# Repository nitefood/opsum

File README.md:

# OPSUM - The Open PSU Meter project

OPSUM is a **DC voltmeter and ammeter board** with 4mm banana socket inputs, that enables measuring and logging **voltage, current and power**, even when using a bench PSU that has no builtin telemetry feature. Communication between the board and the host happens via **UART protocol** over a dedicated USB port that is **galvanically isolated** from the PSU/DUT (*power supply unit and device under test*) side of the PCB, in order to protect the host-side (PC) from potentially destructive shorts or spikes happening on the DUT side.

This repository is structured as a **monorepo**: hardware design files, enclosure CAD files, firmware, host-side GUI tools, release binaries, communication protocol documentation, and third-party GUIs are kept together so you can build, flash, and evolve the project starting from a single source of truth.

## Features

#### Current

- **Real-time voltage, current, and power monitoring** based on the [INA226](https://www.ti.com/product/INA226) monitor IC and the [ESP32-S3](https://www.espressif.com/en/products/socs/esp32-s3) SoC.
- [Kelvin-sensed](https://en.wikipedia.org/wiki/Four-terminal_sensing) shunt layout and full noise filtering (as per TI's [datasheet](https://www.ti.com/lit/ds/symlink/ina226.pdf), chapter *6.4.2 "Filtering and Input Considerations"*) for improved measurement accuracy.
- **Reverse-polarity**, **overvoltage**, and **negative-voltage** protection circuitry.
- PMOS input protection stage with zener-clamped gate drive.
- TVS + Schottky protected INA VBUS input.
- **Galvanic isolation** protecting the host-side USB port from the PSU/DUT side.
- Handles up to **36 V** bus voltage and **20 A** current.
- Compact, low-cost, fully **open source hardware, firmware and software** project.

#### Planned

- I<sup>2</sup>C display showing real time telemetry from the board *(I<sup>2</sup>C pin header for the display is already present on the PCB, only needs designing the enclosure lid opening and in-firmware support)*

## Images
Enclosure render (outside) | Enclosure render (inside)
| - | - |
|  |  |

PCB Layout | PCB 3D View
| - | - |
 |  |

3D printed enclosure (top view) | 3D printed enclosure (sockets visible)
| - | - |
|  |  |

#### 3D printed enclosure (internal 12AWG wiring)

#### [Farmtech's PSU monitor](/third_party_tools/farmtech/) displaying telemetry coming from a live OPSUM board

---

## Quick Start

If you want to build the project yourself, the step-by-step approach is:

1. **Manufacture the board** using a third party PCB fab house (I've used [JLCPCB](https://jlcpcb.com/?from=DUYEWB) with great results, so tolerances and specs are guaranteed to comply with their capabilities, but any fab house should be easily capable to manufacture this board). **Gerbers, BOM and CPL** files alongside required production settings and instructions for PCB manufacturing and assembly are all in the [hardware](/hardware/) section.
	> Disclaimer: the JLCPCB link above is a referral URL, I get a little kickback if you use it to subscribe or buy from them. Thanks for your support!
2. **Solder the remaining through-hole components on the PCB** using the instruction under [howto-build](/howto-build/). I've included a bill of material for THT and hand-assembly components required to complete the project, complete with links to AliExpress to source them.
3. **First-flash the new ESP32-S3 board** with the `-FULL` image (using `esptool`). Prebuilt binaries and usage instructions for `esptool` are in the [dist](dist/) section.
4. **3D print the enclosure and assemble the finished product**. Instructions are under [enclosure](/enclosure/).
5. **Connect the USB port to your PC and use a client-side program** to interface with the OPSUM board and receve its readings. I've included a [minimal GUI](dist/opsum_gui.exe), alongside with fully featured [third party tools](third_party_tools/) compatibile with OPSUM's core firmware [protocol](./protocol-specs/core-uart.md).

If you want to flash a different firmware, or update/reflash the core firmware in the future, there is **no need to disassemble the board** to access the native MCU USB port. Just use the **isolated USB port** with the included [flash tool](dist/flashtool.exe), and reflash the board using a `-OTA` image. OPSUM's main firmware OTA image is packaged under [dist](dist/) as well.

## Open Tooling Approach

This repository includes everything, ranging from the basic OPSUM GUI plus third-party client-side tools that support the Core firmware communication protocol, to enclosure CAD models, PCB layout design files, assembly guides and protocol specification documentation.

You are free to use whichever compatible client (or firmware) matches your needs.

## Repository Layout

| Folder | Contents |
| - | - |
| [dist/](dist/) | release binaries + compilation and flash instructions |
| [protocol-specs/](protocol-specs/) | **DFU** (flashing) and **UART** (runtime communication with the host) protocol specs |
| [src/Firmware/](src/Firmware/) | **Core** (main) and **DFU** (flash update mode) firmware source code |
| [src/GUI/](src/GUI/) | host-side GUI tools source code root folder |
| [src/GUI/flash-tool/](src/GUI/flash-tool/) | desktop DFU flashing GUI source code |
| [src/GUI/opsum-gui/](src/GUI/opsum-gui/) | minimal OPSUM runtime GUI frontend source code |
| [third_party_tools/](third_party_tools/) | bundled alternative host-side tools and board-side firmware binaries |
| [hardware/](hardware/) | schematic, PCB layout, BOM, CPL, Gerbers and manufacturing guide |
| [enclosure/](enclosure/) | CAD files for the OPSUM case |
| [howto-build/](howto-build/) | Manual assembly and soldering step-by-step instructions for the OPSUM board project |

## Contributing

**OPSUM is inteded as an open, community driven project**. Anyone is welcome to contribute to it by creating or improving client-side tools, firmware, enclosure, PCB design, protocol specs or documentation!

## Acknowledgements

This project was born out of the desire to improve my PCB design skills, and to document a complete DIY approach to getting a full featured ammeter from scratch, instead of buying one.

In this endeavor, I've received a lot of precious support and ideas from the [JFIXX](https://www.youtube.com/@JFIXX1) community. If you want to join us to say hello, his [discord](https://discord.gg/TcsUshz67p) server is a welcoming and friendly place, full of very skilled and amazing techs!

## Supporting the project

If you like this project and want to support it, you can do so by clicking the button below. Thank you! <3

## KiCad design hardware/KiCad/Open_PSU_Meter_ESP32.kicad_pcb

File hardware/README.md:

# Hardware Design Files

---

---

## Folder contents

This folder hosts electrical and manufacturing design assets for the OPSUM PCB.

## CAD software used

- The OPSUM PCB was designed entirely using the [KiCad v10.0](https://www.kicad.org/) EDA software.

- PCBs were manufactured using [JLCPCB](https://jlcpcb.com/?from=DUYEWB).

	> Disclaimer: the JLCPCB link above is a referral URL, I get a little kickback if you use it to subscribe or buy from them. Thanks for your support!
- Production files were generated by using the excellent [kicad-jlcpb-tools](https://github.com/bouni/kicad-jlcpcb-tools) KiCad plugin.

## Folder structure

| Folder/File name | Content |
| - | - |
| [schematic/](./schematic/) | Full board schematic in .PDF format |
| [KiCad/](./KiCad/) | KiCad project files for schematic and PCB layout |
| [jlcpcb/](./jlcpcb/) | BOM (Bill of Materials), CPL (Component Placement List), Gerber manufacturing outputs |

## Step-by-step Manufacturing Guide (for JLCPCB)

1. Login to [JLCPCB](https://jlcpcb.com/?from=DUYEWB) and click the **Get Instant Quote** button
2. Click "Add gerber file" and upload the [Gerber .zip archive](./jlcpcb/production_files/GERBER-Open_PSU_Meter_ESP32.zip)
3. Layers count and PCB size will be both autodetected from the Gerber files. You can leave all settings as they are. Optionally, you may prefer setting `Surface Finish` to *LeadFree HASL*, but the default will do just fine
4. Scroll to the bottom of the page and enable the **PCB Assembly** toggle. Keep the default values there as well
5. Ensure you pick the desired **PCBA Qty** value: this will determine how many of the manufactured PCBs will also get their SMT components assembled
6. Click Next, then Next.
7. Add the [BOM](./jlcpcb/production_files/BOM-Open_PSU_Meter_ESP32.csv) and [CPL](./jlcpcb/production_files/CPL-Open_PSU_Meter_ESP32.csv) files, then click  **Process BOM & CPL**
8. Ignore the warning (*"The below parts won't be assembled due to data missing.
U3,PS1 designators don't exist in the BOM file."*). This is intentional, since those parts (ESP32-S3-Zero breakout board and isolated DC/DC converter) are to be sourced externally and hand soldered on the PCB. Refer to the [howto-build](../howto-build/) guide for details.
9. Review the matched parts and ensure all are in stock. Click Next.
10. **Carefully check part orientation on the board**. Sometimes their automated system fails to correctly orient the components on the pads. In my case, I had to re-orient **U1** and **Q1**. Just **click the component to select it**, and **press the space key** until they're in the correct orientation (the purple dot should align with the white silkscreen dot/arrow). They should look like this:

	| U1 | Q1 |
	| - | - |
	|  |  |
11. Click Next and pick "*Research/Education/DIY/Entertainment*" -> "*DIY Hobby Circuit Board - HS Code 902300*" from the product description dropdown, then click **Save to Cart**
12. Select the cart item (PCB Manufacture + PCBA) and proceed to Secure Checkout. You will be able to pick a shipping method, enter your shipping address, and complete the order.

## Hand Soldering Guide for through hole components

Once the board is manufactured and the enclosure is printed, refer to the [How To Build](../howto-build/) section to finish assembling the tool.

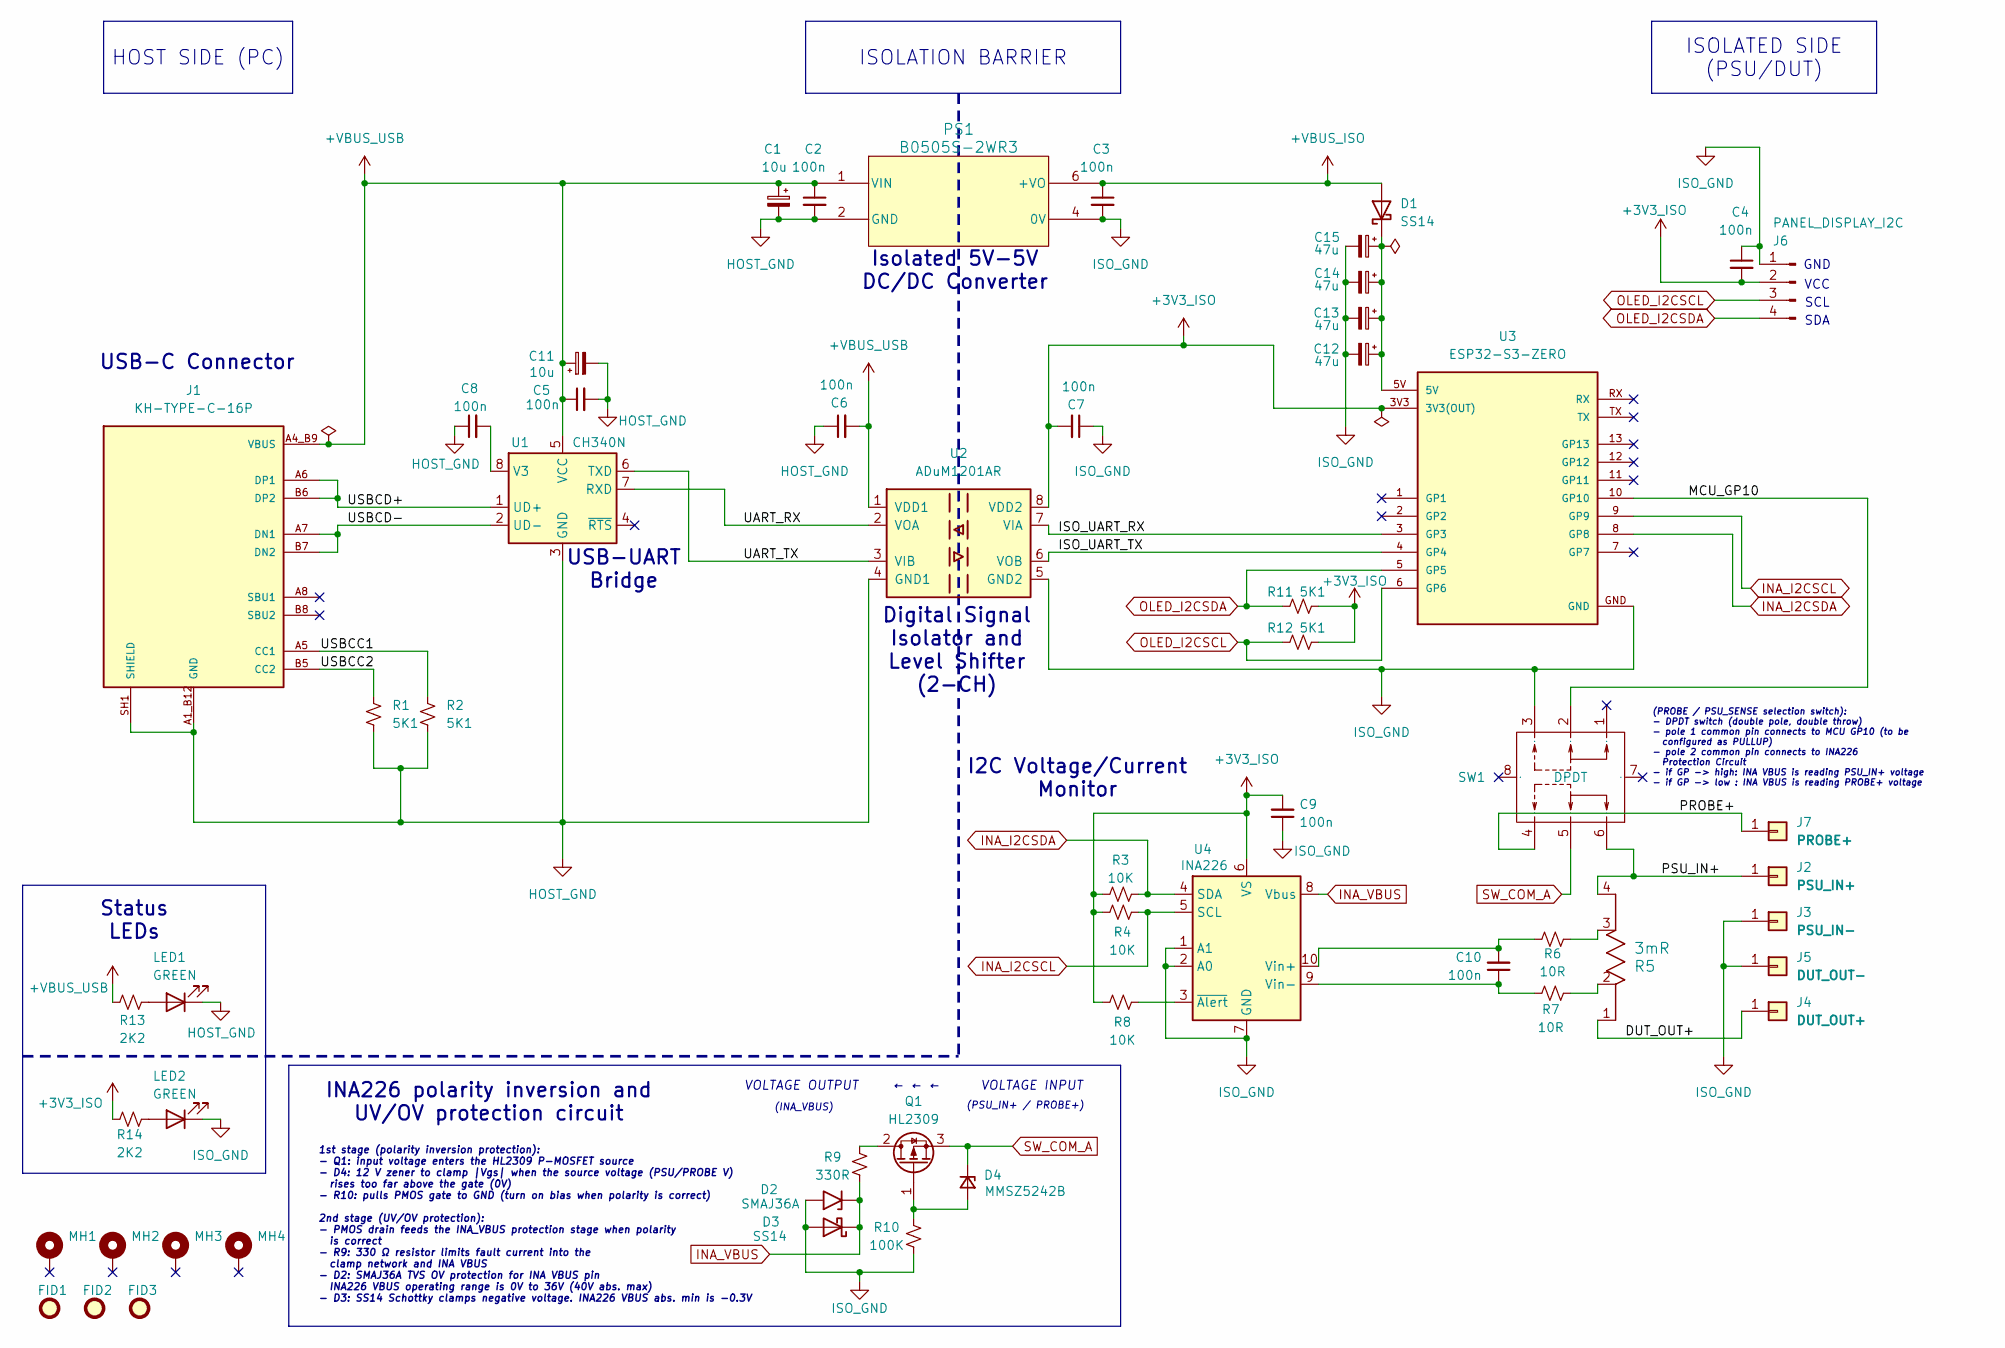
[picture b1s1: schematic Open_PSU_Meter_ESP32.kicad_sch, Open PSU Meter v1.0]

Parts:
C1, C11: 10u; C_1206_3216Metric; Manufacturer Part Number CL31A106KBHNNNE; LCSC C13585
C2, C3, C4, C5, C6, C7, C8, C9, C10: 100n; C_0603_1608Metric; Manufacturer Part Number CC0603KRX7R9BB104; LCSC C14663
C12, C13, C14, C15: 47u; C_1206_3216Metric; Manufacturer Part Number CL31A476MPHNNNE; LCSC C96123
D1, D3: SS14; D_SMA; Manufacturer Part Number SS14; LCSC C2480
D2: SMAJ36A; D_SMA; Manufacturer Part Number SMAJ36A; LCSC C19077550
D4: MMSZ5242B; D_SOD-123; Manufacturer Part Number MMSZ5242B; LCSC C19077426
FID1, FID2, FID3: Fiducial; Fiducial_1mm_Mask2mm
J1: KH-TYPE-C-16P; KINGHELM_KH-TYPE-C-16P; PARTREV A0; LCSC C709357
J2: PSU_IN+
J3: PSU_IN-
J4: DUT_OUT+
J5: DUT_OUT-
J6: PANEL_DISPLAY_I2C; PinHeader_1x04_P2.54mm_Vertical
J7: PROBE+
LED1, LED2: GREEN; LED_0805_2012Metric; Manufacturer Part Number KT-0805G; LCSC C2297
MH1, MH2, MH3, MH4: MountingHole_Pad; MountingHole_2.7mm_M2.5_Pad_Via
PS1: B0505S-2WR3; B_S-2WR2_MNS
Q1: HL2309; SOT-23-3; Manufacturer Part Number HL2309; LCSC C28646263
R1, R2, R11, R12: 5K1; R_0603_1608Metric; Manufacturer Part Number 0603WAF5101T5E; LCSC C23186
R3, R4, R8: 10K; R_0402_1005Metric; Manufacturer Part Number 0402WGF1002TCE; LCSC C25744
R5: 3mR; WSL3637_VIS; Manufacturer Part Number WSL36373L000FEA; LCSC C844085
R6, R7: 10R; R_0402_1005Metric; Manufacturer Part Number TC0225B100JTCC; LCSC C517445
R9: 330R; R_0402_1005Metric; Manufacturer Part Number 0402WGF3300TCE; LCSC C25104
R10: 100K; R_0402_1005Metric; Manufacturer Part Number 0402WGF1003TCE; LCSC C25741
R13, R14: 2K2; R_0603_1608Metric; Manufacturer Part Number 0603WAF2201T5E; LCSC C4190
SW1: DPDT; SW-TH_SK22D02G5; Manufacturer Part SK22D02G5; LCSC Part Name SK22D02G5
U1: CH340N; JEITA_SOIC-8_3.9x4.9mm_P1.27mm; Manufacturer Part Number CH340N; LCSC C2977777
U2: ADuM1201AR; SOIC-8_3.9x4.9mm_P1.27mm; Manufacturer Part Number ADUM1201ARZ-RL7; LCSC C9669
U3: ESP32-S3-ZERO; MODULE_ESP32-S3-ZERO; PARTREV NA
U4: INA226; TSSOP-10_3x3mm_P0.5mm; Manufacturer Part Number INA226AIDGSR; LCSC C49851

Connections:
+3V3_ISO: C4.2, C7.2, C9.2, J6.2, R3.1, R4.2, R8.2, R11.1, R12.1, R14.2, U2.8 (VDD2), U3.3V3 (3V3(OUT)), U4.6 (VS)
+VBUS_ISO: C3.1, D1.2 (A), PS1.6 (+VO)
+VBUS_USB: C1.1, C2.1, C5.1, C6.2, C11.1, J1.A4_B9 (VBUS), J1.A9_B4 (VBUS), PS1.1 (VIN), R13.1, U1.5 (VCC), U2.1 (VDD1)
/DUT_OUT+: J4.1, R5.1
/ISO_UART_RX: U2.7 (VIA), U3.3 (GP3)
/ISO_UART_TX: U2.6 (VOB), U3.4 (GP4)
/MCU_GP10: SW1.2, U3.10 (GP10)
/PROBE+: J7.1, SW1.4
/PSU_IN+: J2.1, R5.4, SW1.6
/UART_RX: U1.7 (RXD), U2.2 (VOA)
/UART_TX: U1.6 (TXD), U2.3 (VIB)
/USBCC1: J1.A5 (CC1), R2.1
/USBCC2: J1.B5 (CC2), R1.1
/USBCD+: J1.A6 (DP1), J1.B6 (DP2), U1.1 (UD+)
/USBCD-: J1.A7 (DN1), J1.B7 (DN2), U1.2 (UD-)
HOST_GND: C1.2, C2.2, C5.2, C6.1, C8.1, C11.2, J1.A1_B12 (GND), J1.A12_B1 (GND), J1.SH1 (SHIELD), J1.SH2 (SHIELD), J1.SH3 (SHIELD), J1.SH4 (SHIELD), LED1.1 (K), PS1.2 (GND), R1.2, R2.2, U1.3 (GND), U2.4 (GND1)
INA_I2CSCL: R4.1, U3.9 (GP9), U4.5 (SCL)
INA_I2CSDA: R3.2, U3.8 (GP8), U4.4 (SDA)
INA_VBUS: D2.1 (A1), D3.1 (K), R9.1, U4.8 (Vbus)
ISO_GND: C3.2, C4.1, C7.1, C9.1, C12.2, C13.2, C14.2, C15.2, D2.2 (A2), D3.2 (A), J3.1, J5.1, J6.1, LED2.1 (K), PS1.4 (0V), R10.2, SW1.3, U2.5 (GND2), U3.GND, U4.1 (A1), U4.2 (A0), U4.7 (GND)
unnamed: C12.1, C13.1, C14.1, C15.1, D1.1 (K), U3.5V
unnamed: D4.2 (A), Q1.1 (G), R10.1
unnamed: LED1.2 (A), R13.2
unnamed: LED2.2 (A), R14.1
unnamed: Q1.2 (D), R9.2
unnamed: R5.2, R7.2
unnamed: R5.3, R6.2
unnamed: C8.2, U1.8 (V3)
unnamed: C10.2, R6.1, U4.10 (Vin+)
unnamed: C10.1, R7.1, U4.9 (Vin-)
unnamed: R8.1, U4.3 (~Alert)
OLED_I2CSCL: J6.3, R12.2, U3.6 (GP6)
OLED_I2CSDA: J6.4, R11.2, U3.5 (GP5)
SW_COM_A: D4.1 (K), Q1.3 (S), SW1.5

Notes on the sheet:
SCL
(INA_VBUS)
(PSU_IN+ / PROBE+)
I2C Voltage/Current Monitor
Isolated 5V-5V DC/DC Converter
SDA
Status LEDs
Digital Signal Isolator and Level Shifter (2-CH)
VCC
VOLTAGE OUTPUT ← ← ← VOLTAGE INPUT
GND
INA226 polarity inversion and UV/OV protection circuit
1st stage (polarity inversion protection): - Q1: input voltage enters the HL2309 P-MOSFET source - D4: 12 V zener to clamp |Vgs| when the source voltage (PSU/PROBE V) rises too far above the gate (0V) - R10: pulls PMOS gate to GND (turn on bias when polarity is correct) 2nd stage (UV/OV protection)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
USB-UART Bridge
(PROBE / PSU_SENSE selection switch): - DPDT switch (double pole, double throw) - pole 1 common pin connects to MCU GP10 (to be configured as PULLUP) - pole 2 common pin connects to INA226 Protection Circuit - if GP -> high: INA VBUS is reading PSU_IN+ voltage - if GP -> low : INA VBUS is reading P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
USB-C Connector
ISOLATED SIDE (PSU/DUT)
HOST SIDE (PC)
ISOLATION BARRIER

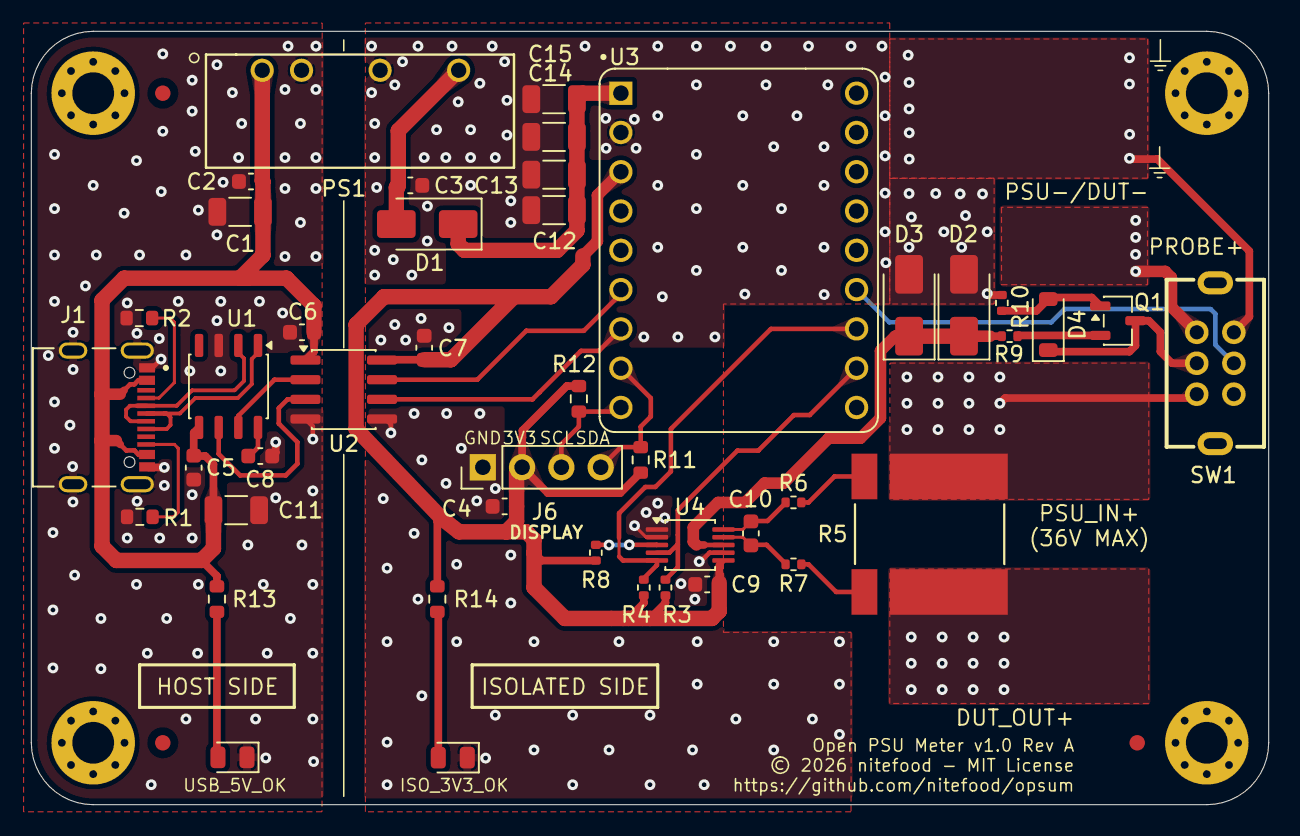
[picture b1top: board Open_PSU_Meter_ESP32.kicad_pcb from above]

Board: 2 copper layers, 80.0 x 50.0 mm, 51 parts (0 on the bottom side), 32 nets.

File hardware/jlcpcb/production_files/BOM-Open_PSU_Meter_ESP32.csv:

Comment,Designator,Footprint,LCSC,Quantity
100K,R10,R_0402_1005Metric,C25741,1
100n,"C10,C2,C3,C4,C5,C6,C7,C8,C9",C_0603_1608Metric,C14663,9
10K,"R3,R4,R8",R_0402_1005Metric,C25744,3
10R,"R6,R7",R_0402_1005Metric,C517445,2
10u,"C1,C11",C_1206_3216Metric,C13585,2
2K2,"R13,R14",R_0603_1608Metric,C4190,2
330R,R9,R_0402_1005Metric,C25104,1
3mR,R5,WSL3637_VIS,C844085,1
47u,"C12,C13,C14,C15",C_1206_3216Metric,C96123,4
5K1,"R1,R11,R12,R2",R_0603_1608Metric,C23186,4
ADuM1201AR,U2,SOIC-8_3.9x4.9mm_P1.27mm,C9669,1
CH340N,U1,JEITA_SOIC-8_3.9x4.9mm_P1.27mm,C2977777,1
DPDT,SW1,SW-TH_SK22D02G5,C22435631,1
GREEN,"LED1,LED2",LED_0805_2012Metric,C2297,2
HL2309,Q1,SOT-23-3,C28646263,1
INA226,U4,TSSOP-10_3x3mm_P0.5mm,C49851,1
KH-TYPE-C-16P,J1,KINGHELM_KH-TYPE-C-16P,C709357,1
MMSZ5242B,D4,D_SOD-123,C19077426,1
SMAJ36A,D2,D_SMA,C19077550,1
SS14,"D1,D3",D_SMA,C2480,2

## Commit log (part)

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2026-06-22 improved main README wording
2026-06-22 readme improvements
2026-06-22 fix typo
2026-06-22 - add JLCPCB step-by-step guide for PCB manufacture and assembly - mention I2C display pin header

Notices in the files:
hardware/KiCad/Open_PSU_Meter_ESP32.kicad_pcb:
© 2026 nitefood - MIT License
